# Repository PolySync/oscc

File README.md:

Open Source Car Control (OSCC) is an assemblage of software and hardware designs that enable computer control of modern cars in order to facilitate the development of autonomous vehicle technology. It is a modular and stable way of using software to interface with a vehicle’s communications network and control systems.

OSCC enables developers to send control commands to the vehicle, read control messages from the vehicle’s OBD-II CAN network, and forward reports for current vehicle control state. Such as steering angle & wheel speeds. Control commands are issued to the vehicle component ECUs via the steering wheel torque sensor, throttle position sensor, and brake position sensor. (Because the gas-powered Kia Soul isn’t brake by-wire capable, an auxiliary actuator is added to enable braking.) This low-level interface means that OSCC offers full-range control of the vehicle without altering the factory safety-case, spoofing CAN messages, or hacking ADAS features.

Although we currently support only the 2014 or later Kia Soul (w/ Kia Soul EV & Kia Niro support coming in Q3/Q4 2017, respectively), the API and firmware have been designed to make it easy to add new vehicle support. Additionally, the separation between API and firmware means it is easier to modify and test parts of your program without having to update the flashed OSCC modules.

Our [Wiki](https://github.com/PolySync/OSCC/wiki) is in the process of being updated to reflect the new changes, but contains a bunch of valuable information to help you get started in understanding the details of the system.

# Versions

New versions of the API and the firmware are released periodically as new features are added and bugs are
fixed. **It is of vital importance that you update whenever there is a new version so that you can be certain
you are not using a version with known safety issues.**

There are four versions to be aware of:

* **Sensor Interface Board (throttle and steering):** the version is printed on the front of the shield

* **Vehicle Control Module (EV brakes):** the version is printed on the front of the shield

* **Actuator Control Board (petrol brakes):** the version is printed on the front of the shield

* **API and Firmware:** a single version is shared by both and listed in the [Releases section](https://github.com/PolySync/oscc/releases) of the repository.

The following table can be used to ensure that you use the appropriate firmware version with your boards:

|                        | Board Version | Firmware Version |
| ---------------------- | ------------- | ---------------- |
| Sensor Interface       | >= 1.0.0      | >= 1.0.0         |
| Vehicle Control        | 0.1.0         | >= 1.1.0         |
| Actuator Control       | >= 1.2.0      | >= 1.0.0         |
|                        | < 1.2.0 __*__ | >= 1.0.1         |

__*__ *Later versions of the Actuator Control Board utilize new pins to perform additional safety checks on startup. To use the new firmware on older boards, please see additional instructions in the [build](#brake-startup-test) section.*

# Repository Contents

* **api** - Software API, so your program can seamlessly talk to our modules.
* **firmware** - Arduino libraries and firmware for the OSCC modules.
* **hardware** - PCB schematics and board designs for control modules.

# Boards

The sensor interface and actuator control board schematics and design files are located in the
`hardware/boards` directory. If you don't have the time or fabrication resources, the boards can be
purchased as a kit from the [OSCC website](http://oscc.io).

Thanks to [Trey German](https://www.polymorphiclabs.com) and [Macrofab](https://macrofab.com/) for
help designing and manufacturing the custom boards.

# Building and Uploading Firmware

The OSCC Project is built around a number of individual firmware modules that inter-operate to allow communication with your vehicle.
These modules are built from Arduinos and Arduino shields designed specifically for interfacing with various vehicle components.
Once these modules have been installed in the vehicle and flashed with the firmware, the API can be used to
receive reports from the car and send spoofed commands.

## Pre-requisites

You must have Arduino Core and CMake (version 2.8 or greater) installed on
your machine.

```
sudo apt install arduino-core build-essential cmake
```

OSCC uses CMake to avoid some of the limitations of the Arduino IDE. Using this method you can build
and upload the firmware from the command-line.

Check out [Arduino CMake](https://github.com/queezythegreat/arduino-cmake) for more information.

## Building the Firmware

Navigate to the `firmware` directory and create a build directory inside of it:

```
cd firmware
mkdir build
cd build
```

To generate Makefiles, tell `cmake` which vehicle to build for by supplying the
appropriate build flag:

| Vehicle         | Flag             |
| --------------- | ---------------- |
| Kia Soul Petrol | -DKIA_SOUL=ON    |
| Kia Soul EV     | -DKIA_SOUL_EV=ON |

For example, if you want to build firmware for the petrol Kia Soul:

```
cmake .. -DKIA_SOUL=ON
```

**Operator Overrides: While all OSCC modules have operator override detection enabled by default, attempting to grab the steering wheel while the system is active could result in serious injury. The preferred method of operator override for steering is to utilize the brake pedal or E-stop button. To disable operator override for the steering module, pass an additional flag to the CMake build step.**

```
cmake .. -DKIA_SOUL=ON -DSTEERING_OVERRIDE=OFF
```

If steering operator overrides remain enabled, the sensitivity can be adjusted by changing the value of the `TORQUE_DIFFERENCE_OVERRIDE_THRESHOLD` in the corresponding vehicle's header file.

* Lowering this value will make the steering module more sensitive to operator override, but will result in false positives around high-torque areas, such as the mechanical limits of the steering rack or when quickly and rapidly changing direction.
* Increasing this value will result in fewer false positives, but will make it more difficult to manually override the wheel.

By default, your firmware will have debug symbols which is good for debugging but increases
the size of the firmware significantly. To compile without debug symbols and optimizations
enabled, use the following instead:

```
cmake .. -DKIA_SOUL=ON -DCMAKE_BUILD_TYPE=Release
```

**NOTE:**
> For older (< 1.2.0) versions of the actuator control board, you need to set an additional flag using `cmake .. -DKIA_SOUL=ON -DBRAKE_STARTUP_TEST=OFF` to disable startup tests that are not compatible with the previous board design.

This will generate the necessary files for building.

Now you can build all of the firmware with `make`:

```
make
```

If you'd like to build only a specific module, you can provide a target name to
`make` for whichever module you'd like to build:

```
make brake
make can-gateway
make steering
make throttle
```

## Uploading the Firmware

Once the firmware is successfully built, you can upload it. When you connect to
an Arduino with a USB cable, your machine assigns a serial device to it with the
path `/dev/ttyACM#` where `#` is a digit starting at 0 and increasing by one with
each additional Arduino connected.

You can upload firmware to a single module or to all modules. By default, `cmake`
is configured to expect each module to be `/dev/ttyACM0`, so if you connect a
single module to your machine, you can flash it without changing anything:

```
make throttle-upload
```

However, if you want to flash all modules, you need to change the ports in
`cmake` for each module to match what they are on your machine. The easiest way
is to connect each module in alphabetical order (brake, CAN gateway, steering,
throttle) so that they are assigned `/dev/ttyACM0` through `/dev/ttyACM3` in
a known order. You can then change the ports during the `cmake ..` step:

```
cmake .. -DKIA_SOUL=ON -DSERIAL_PORT_BRAKE=/dev/ttyACM0 -DSERIAL_PORT_CAN_GATEWAY=/dev/ttyACM1 -DSERIAL_PORT_STEERING=/dev/ttyACM2 -DSERIAL_PORT_THROTTLE=/dev/ttyACM3
```

Then you can flash all with one command:

```
make all-upload
```

Sometimes it takes a little while for the Arduino to initialize once connected, so if there is an
error thrown initially, wait a little bit and then retry the command.

## Monitoring Arduino Modules

It is sometimes useful to monitor individual Arduino modules to check for proper operation and to
debug. If the modules have been built with the flag `-DCMAKE_BUILD_TYPE=Debug`, their debug
printing functionality will be enabled and they will print status information to the serial interface.

The GNU utility `screen` is one option to communicate with the Arduino via serial over USB. It can
be used to both receive the output of any `Serial.print` statements in your Arduino code, and to
push commands over serial to the Arduino. If you don't already have it installed,
you can get it with the following command:

```
sudo apt install screen
```

You need to enable debug mode with `-DDEBUG=ON` and tell `cmake` what serial port
the module you want to monitor is connected to
(see [section on uploading](#uploading-the-firmware) for details on the default
ports for each module). The default baud rate is `115200` but you can change it:

```
cmake .. -DKIA_SOUL=ON -DDEBUG=ON -DSERIAL_PORT_THROTTLE=/dev/ttyACM0 -DSERIAL_BAUD_THROTTLE=19200
```

You can use a module's `monitor` target to automatically run `screen`, or a
module's `monitor-log` target to run `screen` and output to a file called
`screenlog.0` in the module's build directory:

```
make brake-monitor
make brake-monitor-log
```

You can exit `screen` with `C-a \`.

To do more in-depth debugging you can use any of a number of serial monitoring applications.
Processing can be used quite effectively to provide output plots of data incoming across a serial
connection.

Be aware that using serial printing can affect the timing of the firmware. You may experience
strange behavior while printing that does not occur otherwise.

# Controlling Your Vehicle - an Example Application

Now that all your Arduino modules are properly setup, it is time to start sending control commands.

We've created an example application, joystick commander, that uses the OSCC API to interface with the firmware, allowing you to send commands using a game controller and receive reports from the on-board OBD-II CAN. These commands are converted into CAN messages, which the OSCC API sends to the respective Arduino modules and are used to actuate the vehicle.

[OSCC Joystick Commander](https://github.com/PolySync/oscc-joystick-commander)

We've also created a ROS node, that uses the OSCC API to interface with the firmware from ROS messages, allowing you to send commands and receive reports in ROS.

[ROSCCO](https://github.com/PolySync/roscco)

# OSCC API

**Open and close CAN channel to OSCC Control CAN.**

```c
oscc_result_t oscc_open( uint channel );
oscc_result_t oscc_close( uint channel );
```

These methods are the start and end points of using the OSCC API in your application. ```oscc_open``` will open a socket connection
on the specified CAN channel, enabling it to quickly receive reports from and send commands to the firmware modules.
When you are ready to terminate your application, ```oscc_close``` can terminate the connection.

**NOTE:**
> The OSCC API catches the SIGIO signal which is asserted when a CAN frame is received on the CAN socket, and sets up a SIGIO signal handler
> to forward valid CAN messages to your application. If you have a section of code that is susceptible to conflicts with interrupts,
> you should temporarily block the SIGIO signal for the duration of that section and unblock it afterward.

**Enable and disable all OSCC modules.**

```c
oscc_result_t oscc_enable( void );
oscc_result_t oscc_disable( void );
```

After you have initialized your CAN connection to the firmware modules, these methods can be used to enable or disable the system. This
allows your application to choose when to enable sending commands to the firmware. Although you can only send commands when the system is
enabled, you can receive reports at any time.

**Publish control command to the corresponding module.**

```c
oscc_result_t publish_brake_position( double normalized_position );
oscc_result_t publish_steering_torque( double normalized_torque );
oscc_result_t publish_throttle_position( double normalized_position );
```

These commands will forward a double value to the specified firmware module. The double values are [0.0, 1.0] for brake and throttle,
and [-1.0, 1.0] for steering where -1.0 is counterclockwise and 1.0 is clockwise. The API will construct the appropriate values to send
as spoofed voltages to the vehicle to achieve the desired state. The API also contains safety checks to ensure no voltages outside of
the vehicle's expected range are sent.

**NOTE:**
> Each of these functions must be called at least once every 200ms to prevent the modules from detecting a loss of communication to the
> controlling computer (at which point they would disable themselves).

**Register callback function to handle OSCC report and OBD messages.**

```c
oscc_result_t subscribe_to_brake_reports( void(*callback)(oscc_brake_report_s *report) );
oscc_result_t subscribe_to_steering_reports( void(*callback)(oscc_steering_report_s *report) );
oscc_result_t subscribe_to_throttle_reports( void(*callback)(oscc_throttle_report_s *report) );
oscc_result_t subscribe_to_fault_reports( void(*callback)(oscc_fault_report_s *report) );
oscc_result_t subscribe_to_obd_messages( void(*callback)(struct can_frame *frame) );
```

In order to receive reports from the modules, your application will need to register a callback handler with the OSCC API.
When the appropriate report for your callback function is received from the API's socket connection, it will then forward the
report to your software.

Each module's reports are described in their respective wiki sections:

* [Brake (EV)](https://github.com/PolySync/oscc/wiki/Firmware-Brake-%28EV%29#brake-report)
* [Brake (Petrol)](https://github.com/PolySync/oscc/wiki/Firmware-Brake-%28Petrol%29#brake-report)
* [Steering](https://github.com/PolySync/oscc/wiki/Firmware-Steering#steering-report)
* [Throttle](https://github.com/PolySync/oscc/wiki/Firmware-Throttle#throttle-report)

In addition to OSCC specific reports, it will also forward any non-OSCC reports to any callback function registered with
```subscribe_to_obd_messages```. This can be used to view CAN frames received from the vehicle's OBD-II CAN channel. If you know
the corresponding CAN frame's id, you can parse reports sent from the car.

# Tests

There are two types of tests available: unit and property-based.

## Test Dependencies

The unit tests and property-based tests each have their own set of dependencies
required to run the tests.

For the unit tests you must have **Cucumber 2.0.0** and its dependency **Boost** installed:

```
sudo apt install ruby-dev libboost-dev
sudo gem install cucumber -v 2.0.0
```

For the property-based tests you must have **Rust**, its build manager **Cargo**, its toolchain manager **rustup**, and **libclang**:

[Rust installation guide](https://www.rust-lang.org/en-US/install.html)

The property-based tests for the API run against the 1.20.0 Rust toolchain, so it will need to be installed via **rustup** if it isn't already. 
`rustup install 1.20.0`

```
sudo apt install clang libclang-dev
```

## Running Tests

Building and running the tests is similar to the firmware itself, but you must instead tell
`cmake` to build the tests instead of the firmware with the `-DTESTS=ON` flag. We also pass
the `-DCMAKE_BUILD_TYPE=Release` flag so that `cmake` will disable debug symbols and enable
optimizations, good things to do when running tests to ensure nothing breaks with
optimizations. Lastly, you must tell the tests which vehicle header to use for
the tests (e.g., `-DKIA_SOUL=ON`).

```
cd firmware
mkdir build
cd build
cmake .. -DTESTS=ON -DCMAKE_BUILD_TYPE=Release -DKIA_SOUL=ON
```

### Unit Tests

Each module has a suite of unit tests that use **Cucumber** with **Cgreen**. There are pre-built
64-bit Linux versions in `firmware/common/testing/framework`.

Boost is required for Cucumber-CPP and has been statically linked into `libcucumber-cpp.a`.
If you need to build your own versions you can use the provided script `build_test_framework.sh`
which will install the Boost dependencies (needed for building), clone the needed
repositories with specific hashes, build the Cgreen and Cucumber-CPP libraries,
and place static Boost in the Cucumber-CPP library.

The built libraries will be placed in an `oscc_test_framework` directory in the
directory that you ran the script from. You can then copy `oscc_test_framework/cucumber-cpp`
and `oscc_test_framework/cgreen` to `firmware/common/testing/framework`.

We can run all of the unit tests available:

```
make run-unit-tests
```

Each module's test can also be run individually:

```
make run-brake-unit-tests
make run-can-gateway-unit-tests
make run-steering-unit-tests
make run-throttle-unit-tests
```

If everything works correctly you should see something like this:

```
# language: en
Feature: Receiving commands

  Commands received from a controller should be processed and acted upon.

  Scenario Outline: Enable throttle command sent from controller        # firmware/throttle/tests/features/receiving_commands.feature:8
    Given throttle control is disabled                                  # firmware/throttle/tests/features/receiving_commands.feature:9
    And the accelerator position sensors have a reading of <sensor_val> # firmware/throttle/tests/features/receiving_commands.feature:10
    When an enable throttle command is received                         # firmware/throttle/tests/features/receiving_commands.feature:12
    Then control should be enabled                                      # firmware/throttle/tests/features/receiving_commands.feature:14
    And the last command timestamp should be set                        # firmware/throttle/tests/features/receiving_commands.feature:15
    And <dac_a_val> should be written to DAC A                          # firmware/throttle/tests/features/receiving_commands.feature:16
    And <dac_b_val> should be written to DAC B                          # firmware/throttle/tests/features/receiving_commands.feature:17

    Examples:
      | sensor_val | dac_a_val | dac_b_val |
      | 0          | 0         | 0         |
      | 256        | 1024      | 1024      |
      | 512        | 2048      | 2048      |
      | 1024       | 4096      | 4096      |
```

### Property-Based Tests

The throttle, steering, and brake modules, along with the PID controller library, also contain a series of
property-based tests.

We can run all of the property-based tests available:

```
make run-property-tests
```

Each module's test can also be run individually:

```
make run-brake-property-tests
make run-steering-property-tests
make run-throttle-property-tests
make run-pid-library-property-tests
```

Once the tests have completed, the output should look similar to the following:

```
running 7 tests
test check_integral_term ... ok
test check_derivative_term ... ok
test check_proportional_term ... ok
test check_reversed_inputs ... ok
test check_same_control_for_same_inputs ... ok
test check_zeroize ... ok

test result: ok. 7 passed; 0 failed; 0 ignored; 0 measured

   Doc-tests tests

running 0 tests

test result: ok. 0 passed; 0 failed; 0 ignored; 0 measured
```

### All Tests

Finally, as a convenience you can run all available firmware tests:

```
make run-all-tests
```

#### API Property-Based tests

Additionally, the api contains a set of property-based tests. To run these, run CMAKE from a directory within the `api/tests` directory, passing in a flag with the vehicle you want to run the tests for. For example: 

```
cd api/tests
mkdir build
cd build
cmake .. -DKIA_SOUL=ON
```

The tests can then be run using `make run-api-property-tests`. For the tests to run, you must have a vcan interface initialized. The test folder contains a script `initialize_vcan.sh` which can be used to set it up automatically.

# Additional Vehicles & Contributing

OSCC currently has information regarding the Kia Soul PS (2014-2018), but we want to grow! The
repository is structured to facilitate including more vehicles as more is learned about them.

In order to include information related to a new vehicle's specification, follow the format defined in ```api/include/vehicles/kia_soul.h``` and
add a `cmake` option to choose your new header when compiling the API.

Please see [CONTRIBUTING.md](CONTRIBUTING.md).

# License Information

Hardware source materials (e.g. schematics, board layouts, wiring diagrams, data sheets, physical
installation documentation, 3D models, etc.) for the OSCC (Open Source Car Control) Project are
licensed under Creative Commons Attribution-ShareAlike 4.0 International (CC BY-SA 4.0).

Firmware  and software source for the OSCC (Open Source Car Control) Project is licensed under the
MIT License (MIT) unless otherwise noted (e.g. 3rd party dependencies, etc.).

Please see [LICENSE.md](LICENSE.md) for more details.

# Contact Information

Please direct questions regarding OSCC and/or licensing to help@polysync.io.

*Distributed as-is; no warranty is given.*

Copyright (c) 2017 PolySync Technologies, Inc.  All Rights Reserved.

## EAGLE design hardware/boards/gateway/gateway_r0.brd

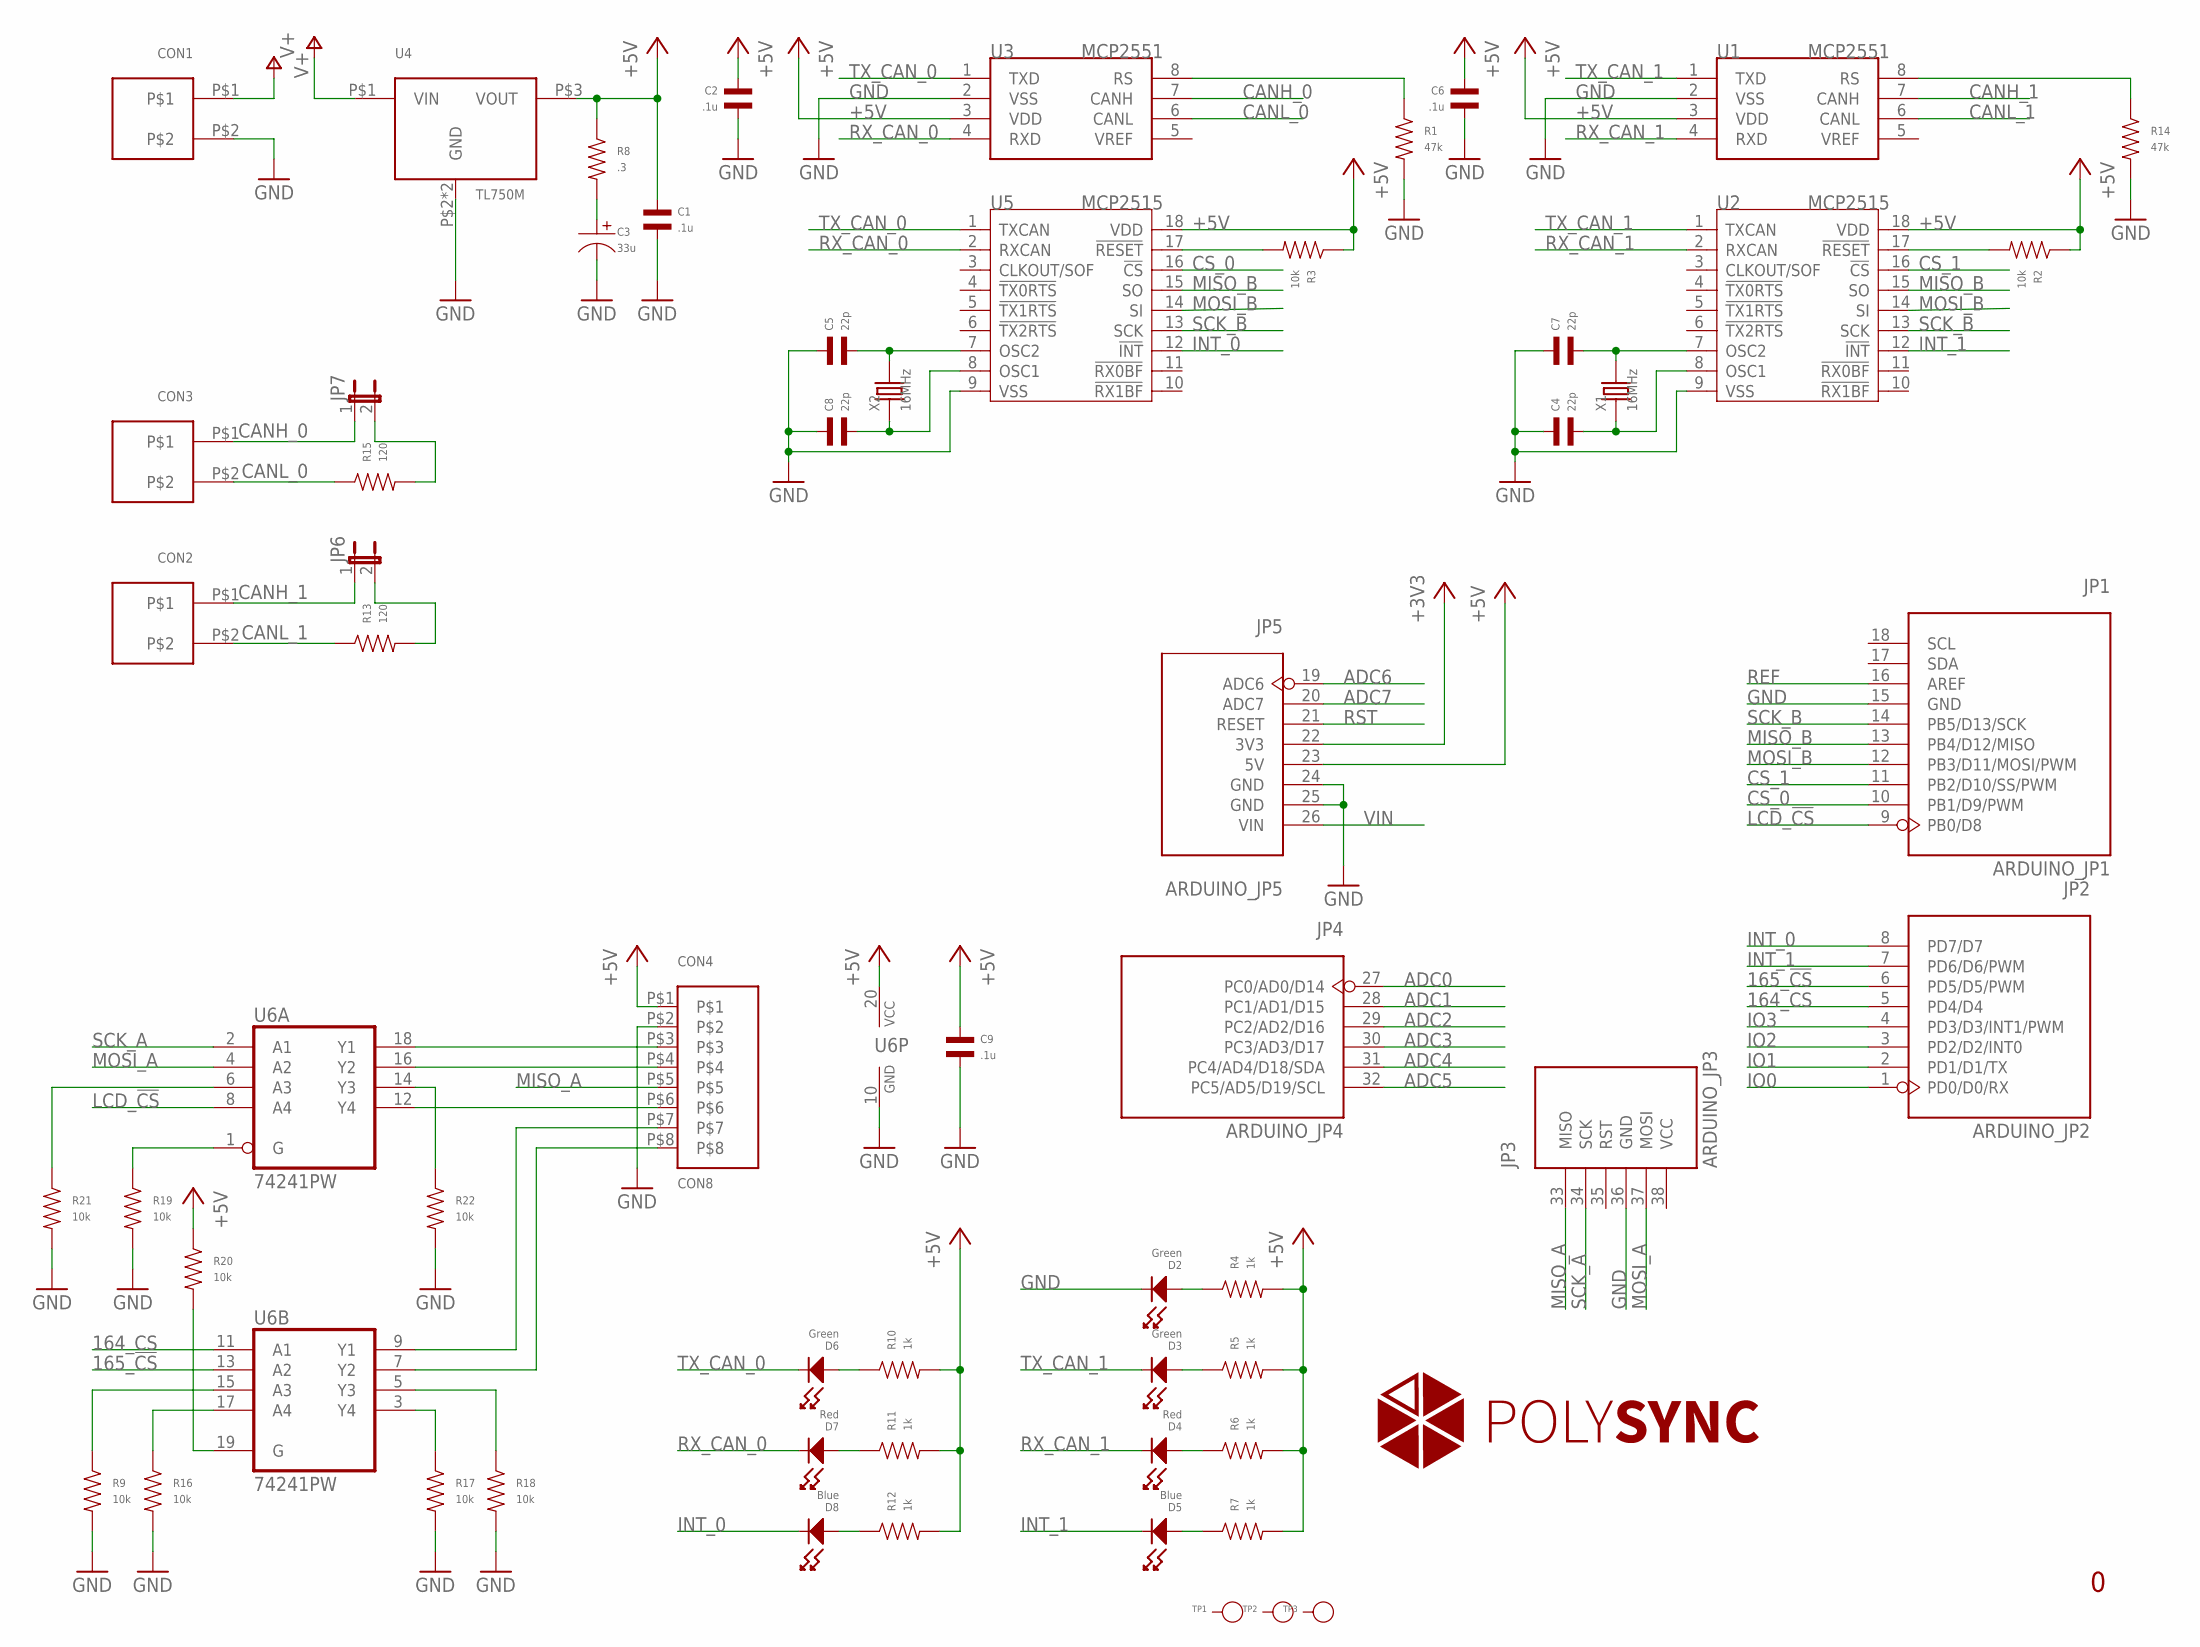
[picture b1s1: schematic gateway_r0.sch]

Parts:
C1, C2, C6, C9: .1u; C0402
C3: 33u; CP1206
C4, C5, C7, C8: 22p; C0402
CON1, CON2, CON3: CON23.5MM; PHOENIX_2_45
CON4: CON8; PH-8-SM
D2, D3, D6: Green; LED0603
D4, D7: Red; LED0603
D5, D8: Blue; LED0603
JP1: ARDUINO_JP1
JP2: ARDUINO_JP2
JP3: ARDUINO_JP3
JP4: ARDUINO_JP4
JP5: ARDUINO_JP5
JP6, JP7: JP1E; JP1
R1, R14: 47k; R0402
R2, R3, R9, R16, R17, R18, R19, R20, R21, R22: 10k; R0402
R4, R5, R6, R7, R10, R11, R12: 1k; R0402
R8: .3; R0402
R13, R15: 120; R0402
TP1, TP2, TP3: PAD-TEST-POINT'4545'; TP_4545
U1, U3: MCP2551; SOIC8-6.0
U2, U5: MCP2515; SOIC18
U4: TL750M; TO-263
U6: 74241PW; PW_R-PDSO-G20
X1, X2: 16MHz; HC49UP

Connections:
164_CS: JP2.5 (PD4/D4), U6.11 (A1)
165_!CS: JP2.6 (PD5/D5/PWM), U6.13 (A2)
+3V3: JP5.22 (3V3)
+5V: C1.P$1, C2.P$1, C6.P$1, C9.P$1, CON4.P$1, JP5.23 (5V), R2.P$1, R3.P$1, R4.P$2, R5.P$2, R6.P$2, R7.P$2, R8.P$1, R10.P$2, R11.P$2, R12.P$2, R20.P$1, U1.3 (VDD), U2.18 (VDD), U3.3 (VDD), U4.P$3 (VOUT), U5.18 (VDD), U6.20 (VCC)
ADC0: JP4.27 (PC0/AD0/D14)
ADC1: JP4.28 (PC1/AD1/D15)
ADC2: JP4.29 (PC2/AD2/D16)
ADC3: JP4.30 (PC3/AD3/D17)
ADC4: JP4.31 (PC4/AD4/D18/SDA)
ADC5: JP4.32 (PC5/AD5/D19/SCL)
ADC6: JP5.19 (ADC6)
ADC7: JP5.20 (ADC7)
CANH_0: CON3.P$1, JP7.1, U3.7 (CANH)
CANH_1: CON2.P$1, JP6.1, U1.7 (CANH)
CANL_0: CON3.P$2, R15.P$1, U3.6 (CANL)
CANL_1: CON2.P$2, R13.P$1, U1.6 (CANL)
CS_0: JP1.10 (PB1/D9/PWM), U5.16 (!CS)
CS_1: JP1.11 (PB2/D10/SS/PWM), U2.16 (!CS)
GND: C1.P$2, C2.P$2, C3.P$2, C4.P$1, C5.P$1, C6.P$2, C7.P$1, C8.P$1, C9.P$2, CON1.P$2, CON4.P$2, D2.CATHODE, JP1.15 (GND), JP3.36 (GND), JP5.24 (GND), JP5.25 (GND), R1.P$2, R9.P$2, R14.P$2, R16.P$2, R17.P$2, R18.P$2, R19.P$2, R21.P$2, R22.P$2, U1.2 (VSS), U2.9 (VSS), U3.2 (VSS), U4.P$2 (GND), U4.P$4 (GND), U5.9 (VSS), U6.10 (GND)
INT_0: D8.CATHODE, JP2.8 (PD7/D7), U5.12 (!INT)
INT_1: D5.CATHODE, JP2.7 (PD6/D6/PWM), U2.12 (!INT)
IO0: JP2.1 (PD0/D0/RX)
IO1: JP2.2 (PD1/D1/TX)
IO2: JP2.3 (PD2/D2/INT0)
IO3: JP2.4 (PD3/D3/INT1/PWM)
LCD_!CS: JP1.9 (PB0/D8), U6.8 (A4)
MISO_A: CON4.P$5, JP3.33 (MISO)
MISO_B: JP1.13 (PB4/D12/MISO), U2.15 (SO), U5.15 (SO)
MOSI_A: JP3.37 (MOSI), U6.4 (A2)
MOSI_B: JP1.12 (PB3/D11/MOSI/PWM), U2.14 (SI), U5.14 (SI)
unnamed: D3.ANODE, R5.P$1
unnamed: JP6.2, R13.P$2
unnamed: C5.P$2, U5.7 (OSC2), X2.2
unnamed: C3.P$1, R8.P$2
unnamed: D4.ANODE, R6.P$1
unnamed: D2.ANODE, R4.P$1
unnamed: C8.P$2, U5.8 (OSC1), X2.1
unnamed: D5.ANODE, R7.P$1
unnamed: R14.P$1, U1.8 (RS)
unnamed: R1.P$1, U3.8 (RS)
unnamed: CON4.P$3, U6.18 (Y1)
unnamed: D6.ANODE, R10.P$1
unnamed: D7.ANODE, R11.P$1
unnamed: D8.ANODE, R12.P$1
unnamed: JP7.2, R15.P$2
unnamed: C7.P$2, U2.7 (OSC2), X1.2
unnamed: C4.P$2, U2.8 (OSC1), X1.1
unnamed: CON4.P$4, U6.16 (Y2)
unnamed: R21.P$1, U6.6 (A3)
unnamed: CON4.P$6, U6.12 (Y4)
unnamed: CON4.P$7, U6.9 (Y1)
unnamed: CON4.P$8, U6.7 (Y2)
unnamed: R9.P$1, U6.15 (A3)
unnamed: R16.P$1, U6.17 (A4)
unnamed: R17.P$1, U6.3 (Y4)
unnamed: R18.P$1, U6.5 (Y3)
unnamed: R19.P$1, U6.1 (G)
unnamed: R20.P$2, U6.19 (G)
unnamed: R22.P$1, U6.14 (Y3)
REF: JP1.16 (AREF)
RST: JP5.21 (RESET)
RST_N: R2.P$2, U2.17 (!RESET)
RST_N1: R3.P$2, U5.17 (!RESET)
RX_CAN_0: D7.CATHODE, U3.4 (RXD), U5.2 (RXCAN)
RX_CAN_1: D4.CATHODE, U1.4 (RXD), U2.2 (RXCAN)
SCK_A: JP3.34 (SCK), U6.2 (A1)
SCK_B: JP1.14 (PB5/D13/SCK), U2.13 (SCK), U5.13 (SCK)
TX_CAN_0: D6.CATHODE, U3.1 (TXD), U5.1 (TXCAN)
TX_CAN_1: D3.CATHODE, U1.1 (TXD), U2.1 (TXCAN)
V+: CON1.P$1, U4.P$1 (VIN)
VIN: JP5.26 (VIN)

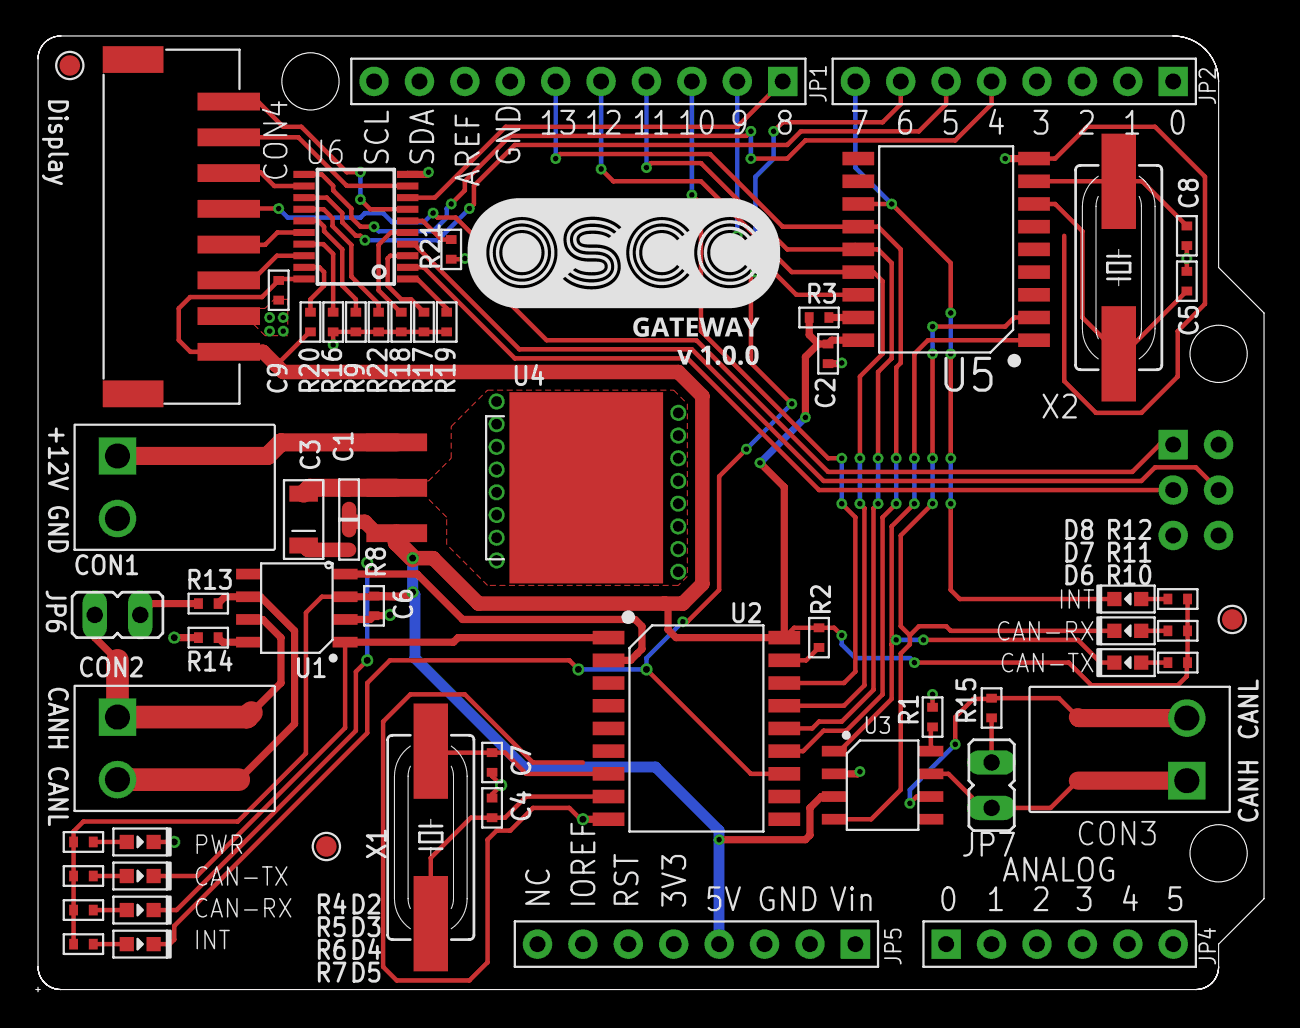
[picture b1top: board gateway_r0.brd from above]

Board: 2 copper layers, 68.6 x 53.3 mm, 62 parts (0 on the bottom side), 55 nets.

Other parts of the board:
U$1: POLYSYNC_STEERING_BOT
U$2: POLYSYNC_GATEWAY_1_0_0

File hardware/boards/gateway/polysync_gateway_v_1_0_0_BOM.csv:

Polysync Gateway Board BOM V1.0.0,,,,,,,,
,,,,,,,,
Quantity,Reference Designator,Description,Mfg,Mfg Part No.,Distributor,Distributor Part No.,Price,Total Price
1,R8,RES SMD 0.3 OHM 1% 1/6W 0402,Panasonic Electronic Components,ERJ-2BQFR30X,Digikey,P.30AKCT-ND,0.59,0.59
10,"R2, R3, R9, R16, R17, R18, R19, R20, R21, R22",RES SMD 10K OHM 1% 1/10W 0402,Panasonic Electronic Components,ERJ-2RKF1002X,Digikey,P10.0KLCT-ND,0.1,1
2,"R13, R15",RES SMD 120 OHM 1% 1/10W 0402,Panasonic Electronic Components,ERJ-2RKF1200X,Digikey,P120LCT-ND,0.1,0.2
7,"R4, R5, R6, R7, R10, R11, R12",RES SMD 1K OHM 1% 1/10W 0402,Panasonic Electronic Components,ERJ-2RKF1001X,Digikey,P1.00KLCT-ND,0.1,0.7
2,"R1, R14",RES SMD 47K OHM 1% 1/10W 0402,Panasonic Electronic Components,ERJ-2RKF4702X,Digikey,P47.0KLCT-ND,0.1,0.2
4,"C1, C2, C6, C9",0.10µF ±10% 16V Ceramic Capacitor X7R 0402 (1005 Metric),Murata Electronics North America,GRM155R71C104KA88J,Digikey,490-6328-1-ND,0.1,0.4
4,"C4, C5, C7, C8","22pF ±5% 50V Ceramic Capacitor C0G, NP0 0402 (1005 Metric)",Murata Electronics North America,GRM1555C1H220JA01J,Digikey,490-11382-1-ND,0.1,0.4
1,C3,33µF ±10% Molded Tantalum Capacitors 10V 1206 (3216 Metric) 1.7 Ohm,AVX Corporation,TAJA336K010RNJ,Digikey,478-8882-1-ND,0.6,0.6
2,"D5, D8",Blue 470nm LED Indication - Discrete 3.2V 0603 (1608 Metric),Wurth Electronics Inc,150060BS75000,Digikey,732-4966-1-ND,0.26,0.52
2,"D4, D7",LED RED CLEAR 0603 SMD,Wurth Electronics Inc,150060RS75000,Digikey,732-4978-1-ND,0.24,0.48
3,"D2, D3, D6",LED GREEN CLEAR 0603 SMD,Wurth Electronics Inc,150060GS75000,Digikey,732-4971-1-ND,0.24,0.72
2,"X1, X2",16MHz ±30ppm Crystal 18pF 40 Ohm -40°C ~ 85°C Surface Mount HC49/US,Abracon LLC,ABLS-16.000MHZ-D-4-T,Digikey,535-13436-1-ND,0.24,0.48
2,"U2, U5",CAN Controller CAN 2.0 SPI Interface 18-SOIC,Microchip Technology,MCP2515-I/SO,Digikey,MCP2515-I/SO-ND,1.82,3.64
2,"U1, U3",1/1 Transceiver Half CAN 8-SOIC,Microchip Technology,MCP2551-I/SN,Digikey,MCP2551-I/SN-ND,1.02,2.04
1,U4,Linear Voltage Regulator IC Positive Fixed 1 Output 5V 750mA DDPAK/TO-263-3,Texas Instruments,TL750M05CKTTR,Digikey,296-20776-1-ND,1.47,1.47
1,U6,IC BUFF/DVR TRI-ST DUAL 20TSSOP,Texas Instruments,SN74AC241PWR,Digikey,296-4309-1-ND,0.75,0.75
1,JP1,"10 Positions Header, Unshrouded Connector 0.100"" (2.54mm) Through Hole Gold or Gold, GXT™",Amphenol FCI,68002-210HLF,Digikey,609-3301-ND,0.44,0.44
2,"JP2, JP5","8 Positions Header, Unshrouded Connector 0.100"" (2.54mm) Through Hole Gold or Gold, GXT™",Amphenol FCI,68000-208HLF,Digikey,609-3257-ND,0.43,0.86
1,JP3,"6 Position Receptacle Connector 0.100"" (2.54mm) Through Hole Gold",Amphenol FCI,68683-303LF,Digikey,609-3582-ND,1.61,1.61
1,JP4,"6 Positions Header, Unshrouded Connector 0.100"" (2.54mm) Through Hole Gold or Gold, GXT™",Amphenol FCI,68000-206HLF,Digikey,609-3256-ND,0.32,0.32
2,"JP6, JP7","2 Positions Header, Unshrouded Connector 0.100"" (2.54mm) Through Hole Gold or Gold, GXT™",Amphenol FCI,77311-118-02LF,Digikey,609-4434-ND,0.18,0.36
3,"CON1, CON2, CON3","2 Position Wire to Board Terminal Block 45° (135°) Angle with Board 0.138"" (3.50mm) Through Hole",Phoenix Contact,1988956,Digikey,277-1779-ND,0.41,1.23
1,CON4 ,CONN HEADER PH SIDE 8POS 2MM SMD,JST Sales America Inc.,S8B-PH-SM4-TB(LF)(SN),Digikey,455-1755-1-ND,0.97,0.97
2,"For JP6, JP7","2 (1 x 2) Position Shunt Connector White Open Top 0.100"" (2.54mm) Gold or Gold, GXT™",Amphenol FCI,68786-102LF,Digikey,609-3121-ND,0.19,0.38
Total,,,,,,,,$20.36

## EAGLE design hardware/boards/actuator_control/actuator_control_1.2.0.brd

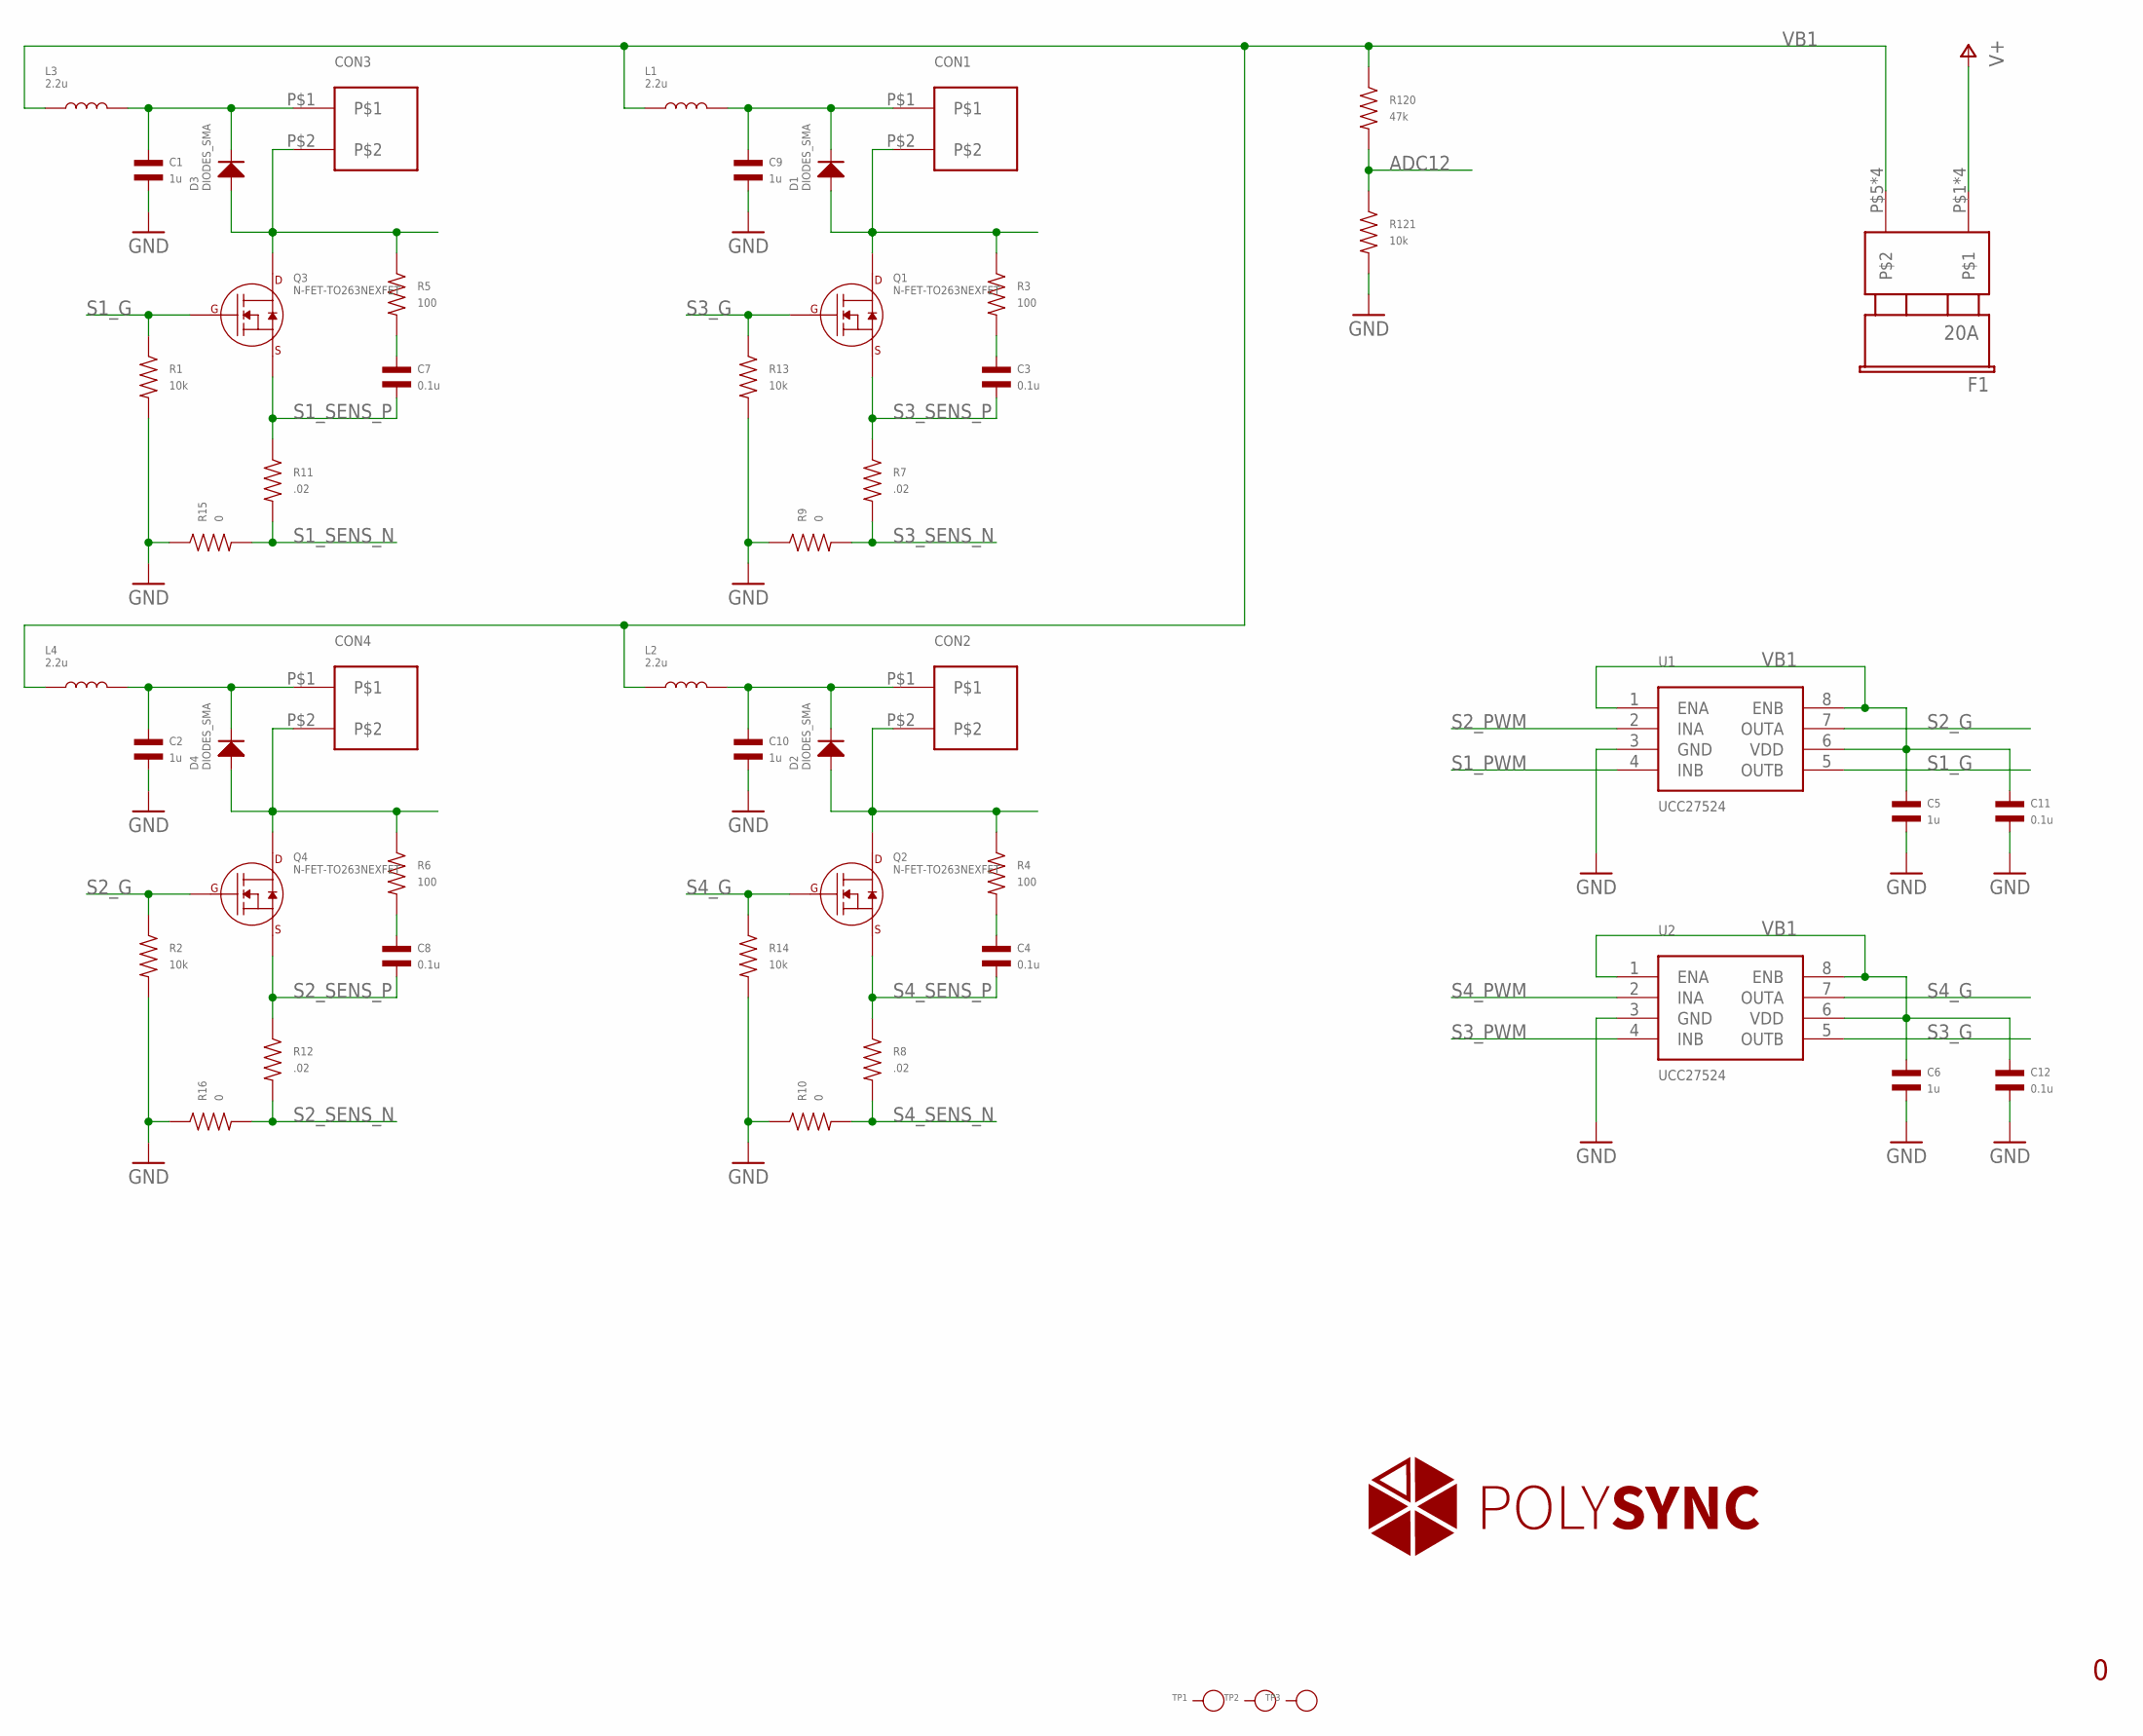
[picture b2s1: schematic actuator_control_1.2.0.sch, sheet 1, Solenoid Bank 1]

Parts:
C1, C2, C5, C6, C9, C10: 1u; C1206
C3, C4, C7, C8, C11, C12: 0.1u; C0805
CON1, CON2, CON3, CON4: CON23.5MM; PHOENIX_2_45
D1, D2, D4: DIODES_SMA; SMA
D3: DIODES_SMA; SMA; MPN US1B-13-F
F1: 20A; FUSE_ATO; PARTNO 178.6165.0001
L1, L2, L3, L4: 2.2u; SRP7050; PARTNO SRP7050TA-2R2M
Q1, Q2, Q3, Q4: N-FET-TO263NEXFET; SON8-DQJ
R1, R2, R13, R14, R121: 10k; R0402
R3, R4, R5, R6: 100; R0805
R7, R8, R11, R12: .02; R1206
R9, R10, R15, R16: 0; R0805
R120: 47k; R0402
TP1, TP2, TP3: PAD-TEST-POINT'4545'; TP_4545
U1, U2: UCC27524; SOIC-8

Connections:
ADC12: R120.P$2, R121.P$1; also elsewhere on the board
GND: C1.P$2, C2.P$2, C5.P$2, C6.P$2, C9.P$2, C10.P$2, C11.P$2, C12.P$2, R1.P$2, R2.P$2, R9.P$1, R10.P$1, R13.P$2, R14.P$2, R15.P$1, R16.P$1, R121.P$2, U1.3 (GND), U2.3 (GND); also elsewhere on the board
unnamed: C1.P$1, CON3.P$1, D3.CATHODE, L3.P$2
unnamed: CON3.P$2, D3.ANODE, Q3.P$5 (DRAIN), Q3.P$6 (DRAIN), Q3.P$7 (DRAIN), Q3.P$8 (DRAIN), Q3.P$9 (DRAIN), R5.P$1
unnamed: C7.P$1, R5.P$2
unnamed: C2.P$1, CON4.P$1, D4.CATHODE, L4.P$2
unnamed: CON4.P$2, D4.ANODE, Q4.P$5 (DRAIN), Q4.P$6 (DRAIN), Q4.P$7 (DRAIN), Q4.P$8 (DRAIN), Q4.P$9 (DRAIN), R6.P$1
unnamed: C8.P$1, R6.P$2
unnamed: C9.P$1, CON1.P$1, D1.CATHODE, L1.P$2
unnamed: CON1.P$2, D1.ANODE, Q1.P$5 (DRAIN), Q1.P$6 (DRAIN), Q1.P$7 (DRAIN), Q1.P$8 (DRAIN), Q1.P$9 (DRAIN), R3.P$1
unnamed: C3.P$1, R3.P$2
unnamed: C10.P$1, CON2.P$1, D2.CATHODE, L2.P$2
unnamed: CON2.P$2, D2.ANODE, Q2.P$5 (DRAIN), Q2.P$6 (DRAIN), Q2.P$7 (DRAIN), Q2.P$8 (DRAIN), Q2.P$9 (DRAIN), R4.P$1
unnamed: C4.P$1, R4.P$2
S1_G: Q3.P$4 (GATE), R1.P$1, U1.5 (OUTB)
S1_PWM: U1.4 (INB); also elsewhere on the board
S1_SENS_N: R11.P$2, R15.P$2; also elsewhere on the board
S1_SENS_P: C7.P$2, Q3.P$1 (SOURCE), Q3.P$2 (SOURCE), Q3.P$3 (SOURCE), R11.P$1; also elsewhere on the board
S2_G: Q4.P$4 (GATE), R2.P$1, U1.7 (OUTA)
S2_PWM: U1.2 (INA); also elsewhere on the board
S2_SENS_N: R12.P$2, R16.P$2; also elsewhere on the board
S2_SENS_P: C8.P$2, Q4.P$1 (SOURCE), Q4.P$2 (SOURCE), Q4.P$3 (SOURCE), R12.P$1; also elsewhere on the board
S3_G: Q1.P$4 (GATE), R13.P$1, U2.5 (OUTB)
S3_PWM: U2.4 (INB); also elsewhere on the board
S3_SENS_N: R7.P$2, R9.P$2; also elsewhere on the board
S3_SENS_P: C3.P$2, Q1.P$1 (SOURCE), Q1.P$2 (SOURCE), Q1.P$3 (SOURCE), R7.P$1; also elsewhere on the board
S4_G: Q2.P$4 (GATE), R14.P$1, U2.7 (OUTA)
S4_PWM: U2.2 (INA); also elsewhere on the board
S4_SENS_N: R8.P$2, R10.P$2; also elsewhere on the board
S4_SENS_P: C4.P$2, Q2.P$1 (SOURCE), Q2.P$2 (SOURCE), Q2.P$3 (SOURCE), R8.P$1; also elsewhere on the board
V+: F1.P$1, F1.P$2, F1.P$3, F1.P$4; also elsewhere on the board
VB1: C5.P$1, C6.P$1, C11.P$1, C12.P$1, F1.P$5, F1.P$6, F1.P$7, F1.P$8, L1.P$1, L2.P$1, L3.P$1, L4.P$1, R120.P$1, U1.1 (ENA), U1.6 (VDD), U1.8 (ENB), U2.1 (ENA), U2.6 (VDD), U2.8 (ENB); also elsewhere on the board
